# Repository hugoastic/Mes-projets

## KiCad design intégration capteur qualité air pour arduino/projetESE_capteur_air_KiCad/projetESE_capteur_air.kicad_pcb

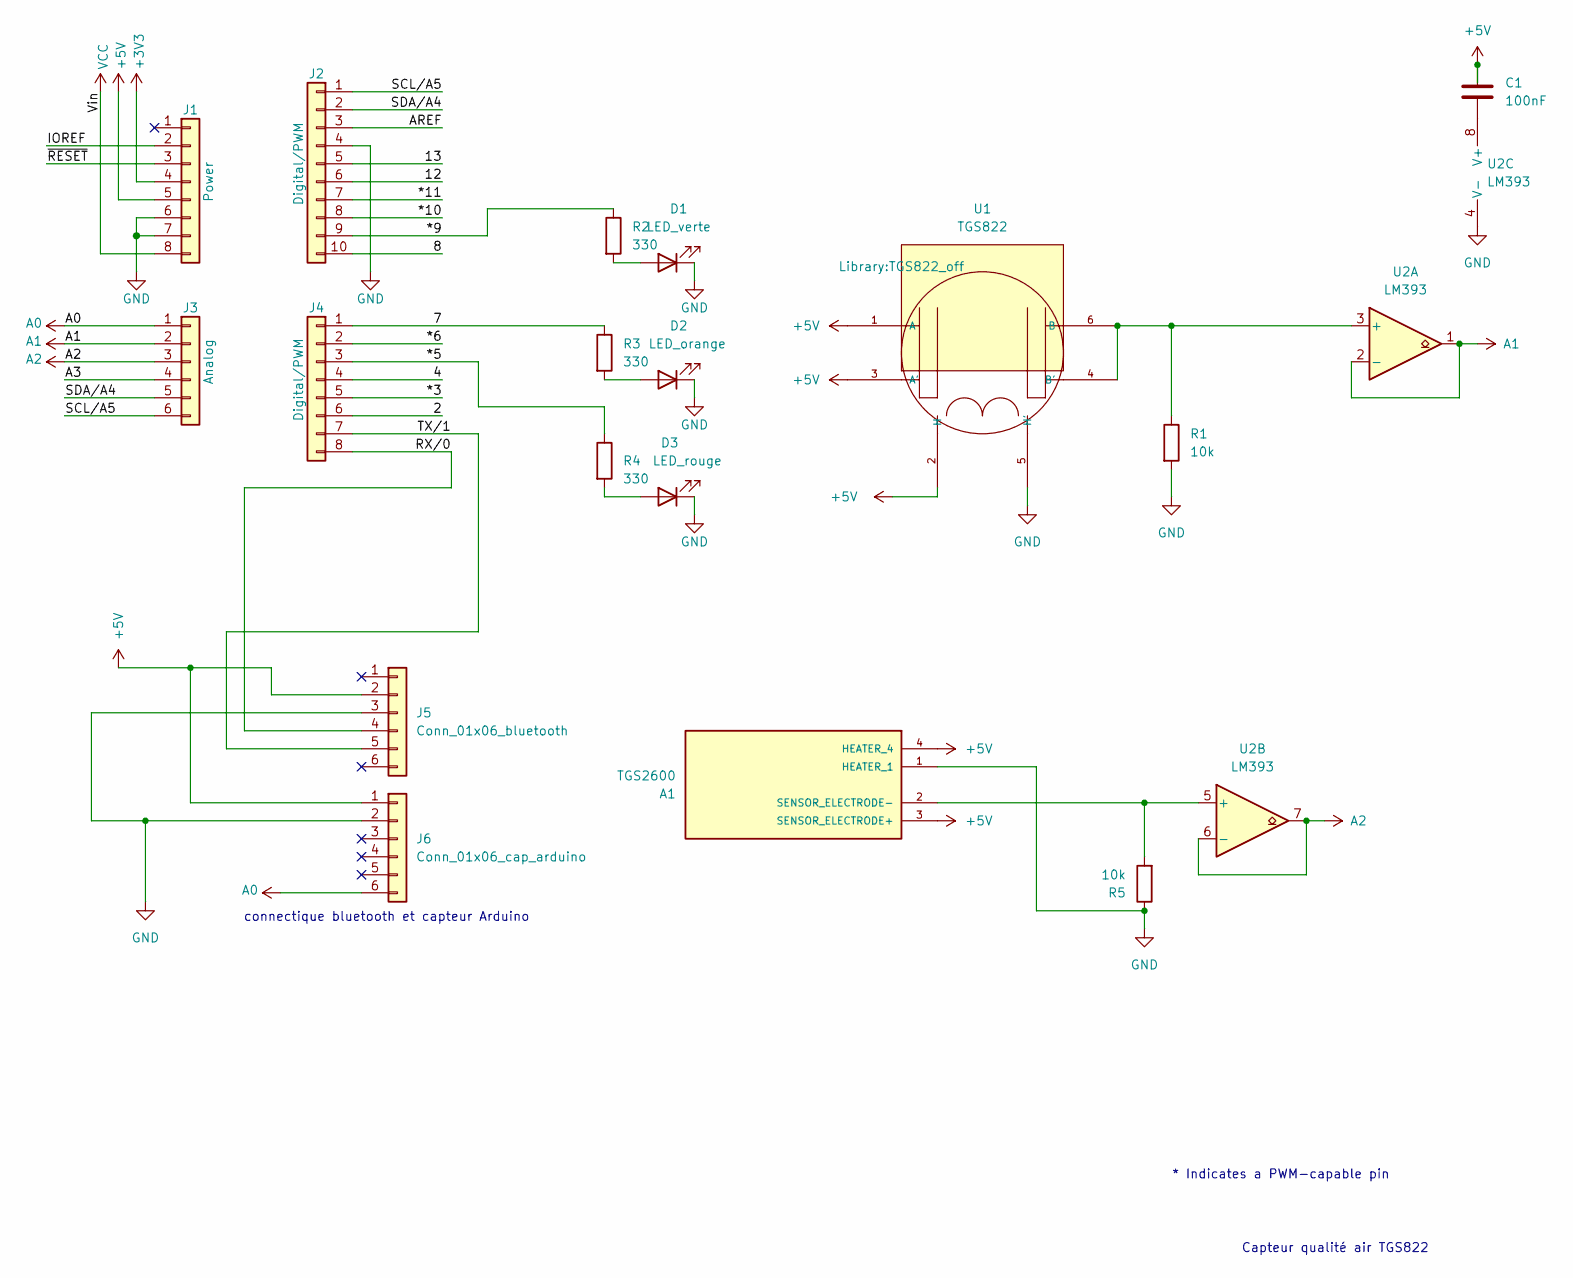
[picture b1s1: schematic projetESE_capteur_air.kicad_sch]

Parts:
A1: TGS2600; TO255P920H830-4; PARTREV 03/22
C1: 100nF; C_0603_1608Metric_Pad1.08x0.95mm_HandSolder
D1: LED_verte; LED_D3.0mm
D2: LED_orange; LED_D3.0mm
D3: LED_rouge; LED_D3.0mm
J1: Power; PinSocket_1x08_P2.54mm_Vertical
J2: Digital/PWM; PinSocket_1x10_P2.54mm_Vertical
J3: Analog; PinSocket_1x06_P2.54mm_Vertical
J4: Digital/PWM; PinSocket_1x08_P2.54mm_Vertical
J5: Conn_01x06_bluetooth; PinSocket_1x06_P2.54mm_Vertical
J6: Conn_01x06_cap_arduino; PinSocket_1x06_P2.54mm_Vertical
R1, R5: 10k; R_0603_1608Metric_Pad0.98x0.95mm_HandSolder
R2, R3, R4: 330; R_0603_1608Metric_Pad0.98x0.95mm_HandSolder
U1: TGS822; TGS822_off
U2: LM393; SO08

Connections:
+3V3: J1.4
+5V: A1.3 (SENSOR_ELECTRODE+), A1.4 (HEATER_4), C1.1, J1.5, J5.2, J6.1, U1.1 (A), U1.2 (H), U1.3 (A')
/2: J4.6
/4: J4.4
/7: J4.1, R3.1
/8: J2.10
/12: J2.6
/13: J2.5
/*3: J4.5
/*5: J4.3, R4.1
/*6: J4.2
/*9: J2.9, R2.1
/*10: J2.8
/*11: J2.7
/A3: J3.4
/AREF: J2.3
/IOREF: J1.2
/RX/0: J4.8, J5.4
/SCL/A5: J2.1, J3.6
/SDA/A4: J2.2, J3.5
/TX/1: J4.7, J5.5
/~RESET: J1.3
A0: J3.1, J6.6
A1: J3.2, U2.1, U2.2 (-)
A2: J3.3, U2.6 (-), U2.7
GND: A1.1 (HEATER_1), D1.1 (K), D2.1 (K), D3.1 (K), J1.6, J1.7, J2.4, J5.3, J6.2, R1.2, R5.1, U1.5 (H'), U2.4 (V-)
unnamed: A1.2 (SENSOR_ELECTRODE-), R5.2, U2.5 (+)
unnamed: D1.2 (A), R2.2
unnamed: D2.2 (A), R3.2
unnamed: D3.2 (A), R4.2
unnamed: R1.1, U1.4 (B'), U1.6 (B), U2.3 (+)
unnamed: C1.2, U2.8 (V+)
VCC: J1.8

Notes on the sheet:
connectique bluetooth et capteur Arduino
* Indicates a PWM-capable pin
Capteur qualité air TGS822

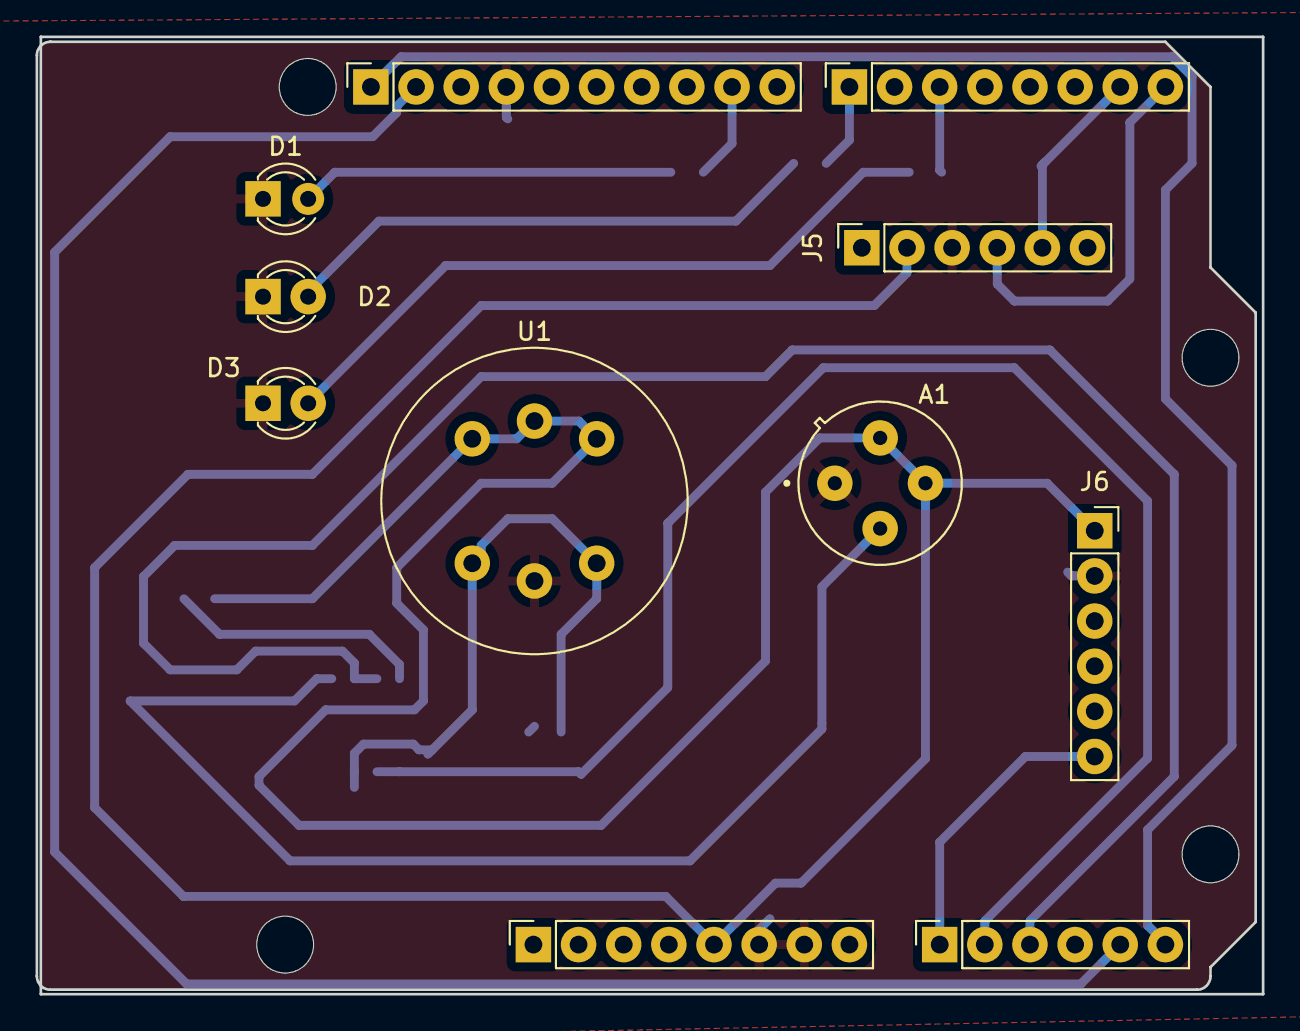
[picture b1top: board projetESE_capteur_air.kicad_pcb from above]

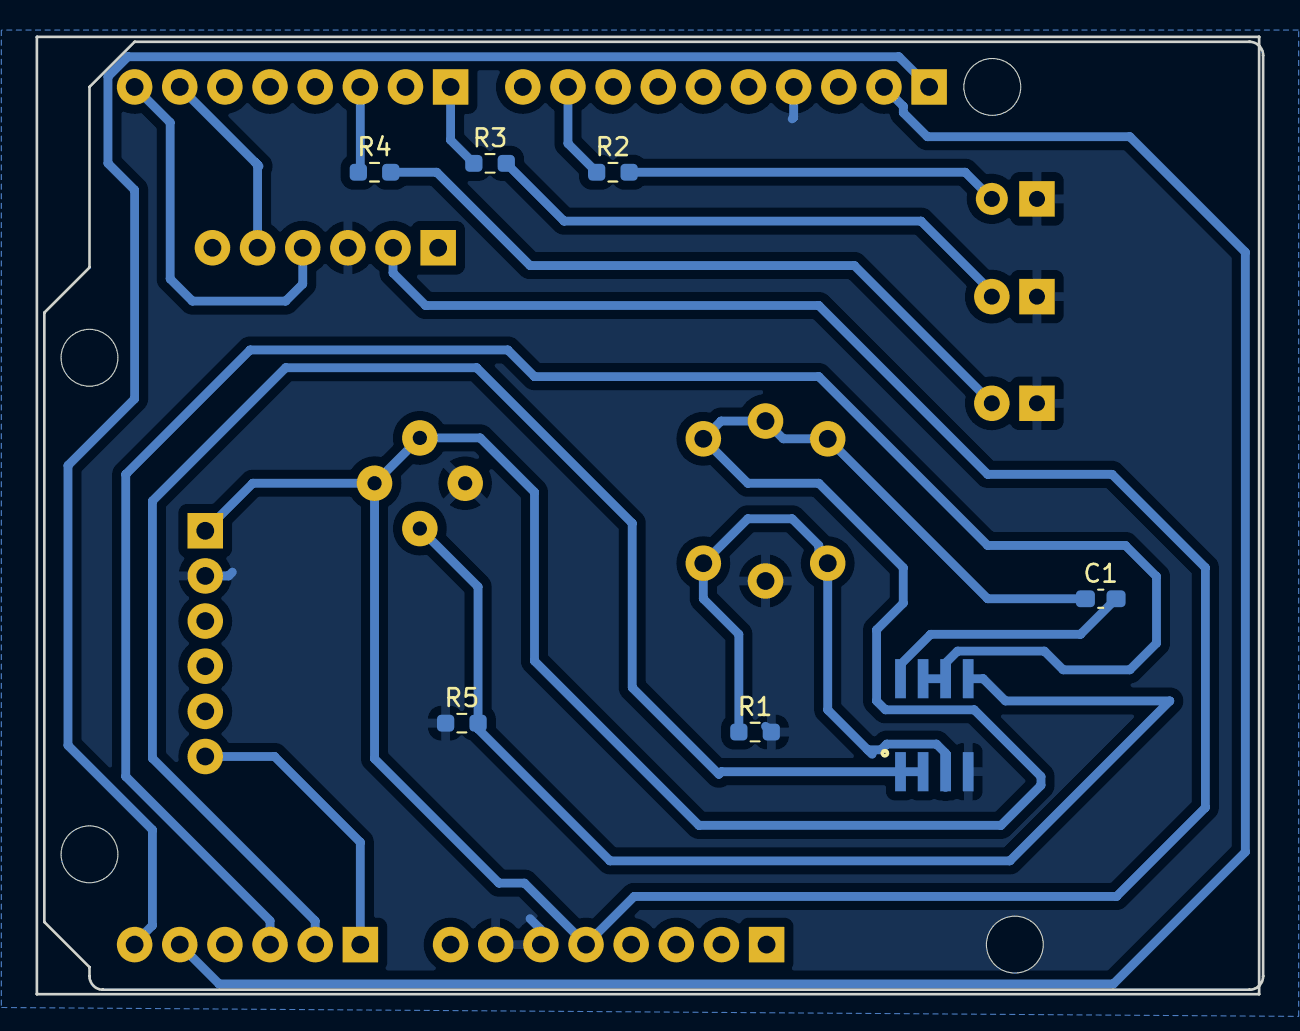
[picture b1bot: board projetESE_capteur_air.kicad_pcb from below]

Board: 2 copper layers, 68.8 x 53.9 mm, 22 parts (7 on the bottom side), 18 nets.

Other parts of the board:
MH1, MH2, MH3, MH4: MountingHole_3.2mm

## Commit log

2024-10-20 Create VHDL_code
2024-12-20 Create y
2025-08-24 Rename CST_Turnstile_antenna.cst to CST_antenna/CST_Turnstile_antenna.cst
2025-09-17 Rename Max gain amplifier_v16.0AWR.emp to Max_gain_amplifier with AWR Design Environment/Max gain amplifier_v16.0AWR.emp
2025-09-24 Projet création réseau de métro en Java
